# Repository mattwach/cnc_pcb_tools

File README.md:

# CNC PCB Tools

This document discusses an entire end-to-end process of milling PCBs with
a "cheap" 3018 CNC machine (although other machines could also apply).

Part of that process, verifying the design and calibrating the machine, are
helped along with simple Python scripts that I created and am giving away
for free.  This document explains how to to use these optional tools in
the appropriate places in the process.

Even if you do not use the tools, I think there this document contains
helpful information, both for beginners and more experienced individuals
looking to compare notes.

### Effort Estimate

This ended up being a long document.  Does that mean that the process takes
a long time?  I don't think it does.  Here are some time estimates:

| Step         | Beginner / Small Project | Experienced / Small Project | Experienced / Medium Project |
|--------------|--------------------------|-----------------------------|------------------------------|
| Design PCB   | 3 hours                  |  1 hour                     | 4 hours                      |
| Create GCode | 1 hour                   |  10 minutes                 | 15 minutes                   |
| CNC Setup    | 1 hour                   |  15 minutes                 | 15 minutes                   |
| CNC Cutting  | 15 minutes               |  15 minutes                 | 1 hour                       |
| Learning     | 1 hour                   |  -                          | -                            |
| **Total**    | **~6 hours**             |  **~2 hours**               | **~ 6 hours**                |

Of course there are many variables.  For example, if you use someone else's
PCB layout, you can cut that out of the time needed.

## Disclaimer

I have tested these tools and process and they work well for me.  That said, I
accept no responsibility for any damage caused to either person or equipment
that occurs from following advice in this document or running any of the
provided or mentioned software.

If you are a beginner to CNC, I have special "Tips" sidebars throughout the
document the CNC section that should be helpful.

## Gallery

Let start by looking at some example results.

First, a fast rise edge generator, as explained in
[this video](https://www.youtube.com/watch?v=9cP6w2odGUc).
This one was created for through-hole parts.

Here is a simple SMD board that uses a 555 and counter chip to make a simple
LED light show.  This one is still on the CNC machine:

Here a simple voltage cutoff circuit I made that combines an ATTiny85,
MOSFET and a fuse for good measure.

Here is an [e-paper based clock](https://github.com/mattwach/epaper_clock)
that I designed earlier this year.  I created
the first copy using a CNC machine, then made 4 more using boards from
a fab.  The first CNC copy was very useful in helping me discover
most of changes I wanted to make to the design (mostly layout) before
submitting the PCB. 

## Why CNC a PCB?

I've tried the following methods:

   * Breadboard
   * Prototype Boards
   * CNC (this doc)
   * Ordering a PCB from a fab, such as [oshpark.com](http://oshpark.com) or [www.pcbway.com](http://www.pcbway.com)

I feel that all of these methods have their place - it just depends on the
project.  Below I'll give my opinion on each one while trying not to go
overboard:

### Breadboard

Breadboards are great for trying something out in a short time.  Parts are
also not "consumed" and can be reused.  Using prebuilt modules as components
makes wiring simple and there are many cheap ones available.

However, any interconnects in your design will be performance limited in terms
of frequency, stray capacitance, unintended resistance and lower reliability.
It's not all bad since you get to exercise some troubleshooting skills and
things seems to work fine most of the time.

Also the method is not suitable for anything permanent.

### Prototype Boards

Like a breadboard but with better reliability and more permanence.  Making
one of these is a bit labor intensive though and there are few economies of
scale when making multiple copies.  Frequency is also usually limited
due to the lack of careful layout, stray capacitances and the lack of
a ground plane.

## CNC

Simple double sided boards are easy (often just a few patch wires are required
on the back side and these can be executed by drilling holes and hand routing
wires on the back).  Complex double sided is possible but requires alignment
techniques that are out-of-scope for this guide.

Performance is excellent.  Both SMD and through-hole components are supported.

Soldering is less convenient than a manufactured PCB due to lack of a solder
mask.  Lack of a silk screen (labeling) means that you may need a PCB printout
to guide component placement.

Requires some learning to be successful - that's the purpose of this document!

### Chemical Etch

I have not tried this one yet (and am meaning to soon) but have read and
watched videos on the process.  Overall, it seems similar to CNC - perhaps a
bit easier to dial in the process and get good results.  There are some clear
downsides however.  One is having to work with some nasty chemicals that
literally dissolve metal.  A second drawback is that drilling holes and cutting
out the board are not handled by the process so you'll have to come up with
something.

## Ordering a PCB

If you need a lot of copies, > 2 layers, or have a complex design, this is your
route.  You also get a solder mask for easier soldering and a silkscreen to
label component and provide other notes.

Turn around latency is around a week.  Cost is in the $20-$60 range assuming
that your board design is perfect.  If not, you'll consume additional weeks and
$$$ on iterations (or you can try to hack in workarounds).

## CNC Trip Points

I think a reason that many people avoid CNC is the upfront learning
curve.  Breaking a bit is easy and the risk of doing so increases
for any of the following reasons:

   1. You use the wrong parameters (feed rate, cut depth) either because you
      don't know or accidently type in the wrong number somewhere.
   2. Your GCode file (which the CNC takes as an input) neglected to command
      the motor to spin up.
   3. You don't zero the machine properly.
   4. You don't build a height map or improperly set one up
   5. Your copper clad is bowed due to improper clamping
   6. You are using unnecessarily aggressive design constraints, such as a
      0.2mm track width when 0.4mm could work for your project.

I'm going to talk about how to mitigate each of the problems about so your
success rate and quality can be quite high.

## Process Overview

Here is an overview of the steps I will cover.  But first, let's acknowledge
that everyone's situation, available tools, and skill sets are different.  The
process I describe below is what works for me, your ideal process will likely
end up being different, but it's good know what works for others.

Also, there could be better or more efficient ways of doing the things I
describe below.  If you think that is the case, let me know!

An overview of the steps:

  * **Design the PCB** (printed circuit board).  Here you create (or get) a
    schematic and layout a PCB.  The PCB you layout can be used for many
    purposes.  For example, you could take the same PCB design, checmical etch
    it, CNC it and send it to a fab.  That said, an "optimal" layout will take
    the final manufacturing process into consideration.
  * **Plot the PCB** design in a universal format know as "Gerber".  Gerber format
    is one that PCB manufacturers will accept as input when then make boards
    for you.  If you are into 3D printing, you can think of Gerber as "STL
    for circuits."
  * **Convert the "Gerber" file to "GCode"**.  GCode is a text file of instructions
    for a specific model of automated machine (CNC machines, 3D printers and 
    others).  The GCode file tells the machine where to cut, how fast to cut,
    how deep to cuts, etc.  None of this information is in the Gerber file -
    the conversion step adds it in.
  * **Setup the machine, execute the `.gcode`**.  
  * **Finishing work**.  Just a little bit of post work for CNC and you are ready for
    soldering.

## Designing your PCB

Some PCB's needs very fine traces and spacing to allow for placement of tiny
SMD components.  These are possible with CNC but not an ideal first project.
While learning, a more forgiving project will help you be
successful as you learn.  Thus my suggested starter project is a simple SMD
button adapter for breadboards.

It's nice because:

   * Simple: No getting sidetracked on how the circuit works
   * Useful: A lot of buttons work so-so when fit in a breadboard.  This one
     give a very solid and reliable connection.
   * Small: It's fast and cheap to iterate and experiment with different
     settings.
   * Forgiving design: Thick traces (1mm) and large clearances (0.4mm) mean
     that the result can be usable even if the settings still need tweaking.

I'm going to use KiCAD.  I used to use Eagle but many agree that KiCAD has
surpassed it.  Eagle and many others will still work fine,
however, as they can all export Gerber plots.  Here is the schematic:

This design has two pin headers and 4 buttons.  For the Pin header PCB
footprint, I'm just using a pin header built into the standard library:

If you are just starting with KiCAD, one way to set the footprint is to click
on it in the schematic, then type "e" to bring up its dialog, where you can
select the footprint:

If this is new information for you, then I suggest watching some of
[John's Basement KiCAD tutorial](https://www.youtube.com/playlist?list=PL3by7evD3F51fKkyrUbH-PCdwPCWc9F8a)
(or similar).

Here are the SMD buttons I chose.  They are 6x3.5mm:

I could not find any footprints for these in the KiCAD library.  The
files probably exist somewhere on the internet, but it's really quite
fast and easy to make a custom one in KiCAD (using the Footprint Editor),
and that is what I did:

[John's Basement, video #12](https://www.youtube.com/watch?v=Rdm5lS_sYsc&list=PL3by7evD3F51fKkyrUbH-PCdwPCWc9F8a&index=14)
demonstrates how to do this.

Of course, you can just use the one I already placed in the `examples/`
folder if you are going with the same button and want to focus more on the
CNC steps.

Here is the completed/routed PCB.

> **Beginner Note** this circuit doesn't have a ground fill place
  because the schematic has no ground, which is a bit unusual.  For a design
  with a ground, you'll want to Google search how to do a "ground fill" in
  KiCAD as it can simplify wiring and help reduce electrical noise in your
  circuit.

One more thing about KiCAD PCB design.  If you choose `File -> Board Setup...`
in the PCB editor, you'll should see a dialog of settings, one of which is
`Design Rules: Constraints`:

Here, there is a "minimum clearance" and "minimum track width" setting that you
can use to make your CNC life easier (in trade for limiting the ability to
route tiny parts).  I think 0.4mm for both settings is a good setting because:

   * You can use bits with a thicker point of contact (e.g. 0.3mm vs 0.1mm).
     Thicker contact points will be harder to break.
   * If you cut a but deeper (or rougher) than expected, the conservative
     minimum track width setting will increase the chance there is still some
     metal there to complete the connection.

of course, this is *just for less-complex designs that can support it*.  Once
you have a dialed-in process, you can push these number as small as you want to
try for.

## Making Gerber & Drill Files

Regardless of what tool I used to design the PCB, I'll need to export the
design in a universal format that the next phase of the process can understand.
These files are known as "Gerber" files and are like a "PDF" or "STL"  for
circuits meaning that they capture only the shapes of the PCB layout and not
other information, such as the associated schematic.

In KiCAD, you create Gerber files using the `File -> Plot`.  Here is the dialog
with the settings I use:

Note that I'm only exporting the F.CU and Edge.Cuts layers.  If you were
sending these files to a Fab, they would want other layers, like the silkscreen
layer, but the CNC machine can not directly make use of these (at least not in
the process I describe here).

This particular design needs holes drilled for the pin headers and
that data needs to be exported too.  "Generate Drill Files..." in the dialog
above will bring up this one.

Output are "PTH" and "NPTH" files.  Those stand for "plated hole" and "non
plated hole".  This design only has plated holes but, if you have mounting
holes, then both files might have some data in them.

## Gerber to GCode (using Flatcam)

There are a number of tools to do this as well.  One that I like is
[Cambam](www.cambam.info), which is a great all-around CNC program that can
import the files above.

But Cambam is not a free program so we are going to go with Flatcam, which is
free.  Flatcam is a bit more complex than it needs to be and is not bug-free
but it get's the job done once you find a navigation path through it's large
set of options.

Let's start the software:

> **Tip** The very first thing I recommend doing is saving your project.
  I also suggest adding the project file to version control.

Let's load up all of the Gerber files

and drill files

and here is the design loaded:

Note the horizontal and vertical red lines.  These will be the [0, 0] origin of
the CNC machine.  It's not in a good spot above because, I forgot to check "Use
drill/place origin" in the KiCAD Gerber plot dialog.  I can go back to KiCAD and
replot but flatcam has a tool as well:

You can put the origin wherever you want and may wonder why I didn't choose the
bottom left corner (as the bottom left aligns better with CNC coordinates).
The reason is because of where I solder my heighmap probe.  I cover the
details in the CNC section.

Now is a good time to save the project.

### Copper Isolation GCode

Now we are going to start making GCode, starting (arbitrarily) with the
copper layer.  Select the copper layer, then "properties":

The properties dialog is a launchpad for doing a number of things.  For the
copper layer, we want to choose "Isolation routing"

Now we are here:

#### Step 1

   * Here we choose the bit type and properties.  These settings are complexity
     overkill, in my opinion.  The intent is that the tool wants to help
     you calculate the needed depth for V bits to get the isolation width
     you want.  The reality is that the tool assumes your machine and process
     have perfect tolerances (e.g. no bit runout, perfect cuts, perfect
     positioning).  If any of these are untrue (and the probably are on a
     3018), then you just end up putting in adjusted numbers anyway to get the
     final result to come out.

   * To keep it simple, I directly choose the final cut width.  I do this
     by choosing a "C1" bit type and typing in the expected cut width.
     I'm essentially telling the tool "trust me, the cuts will be 0.39mm wide".
     If the real cuts are a little wider or narrower, it's usually not a problem
     unless the real cuts are so much wider that you lose copper traces.

   * I chose 0.39mm because I chose 0.4mm isolation widths in KiCAD.  See
     The KiCAD Design section above for a refresher on how I did this.
     **You need to choose a smaller number in flatcam than kicad** or flatcam
     will silently omit traces where it can't fit a line.

   * Keeping it simple makes the "Add from DB" section irrelevant so we can
     skip it.

#### Step 2

   * The main options here are "Passes" and "overlap"

   * Passes are the number of cut lines to make around each trace.

   * Overlap is how much to overlap the passes.  Too little overlap will lead
     to small bit of copper remaining between each pass, which usually isn't a
     big deal, but doesn't look as nice.

   * "Follow" and "Isolation Type" can be kept at default settings.

#### Step 3

   * Create the geometry traces for out next step.  You can actually click
     this button multiple times (presumably with different settings) to
     create multiple geometries - then ignore, hide or delete the
     ones you are not planning to use.

#### Here are results with 3 passes and 25% overlap

#### and 2 passes and 10% overlap

Note that both are included in the project at this point.  I
like the three pass version better so I'm going to right click
on the 2 pass version and delete it.

> **Tip** Now is a good time to save (and possible version control snapshot)

One more step.  At this point we need to create the final gcode file.  To do
this flatcam needs more information.  Click on the geometry object, then properties:

and we are onto this dialog:

#### Step 1

   * This section helps you calculate your cut depth if you are using a V
     bit.  As I said earlier, I find it easier to choose the "C1" bit type
     and put in the depth myself.  Thus if you are following my path,
     **you can simply ignore this section**.

#### Step 2

   * Cut Z: How deep to cut.  A very important parameter.  With a V bit, it also
     will determine your cut width (deeper cuts wider due to the V shape).  Cut 
     depth also has a big effect on how likely you are to break a bit.  **When
     in doubt, choose a small number here, like -0.03** - the penalty of cutting
     too shallow is that you need to cut again deeper which is very quick to do
     with the tools I talk about later (candle_heightmaap_adjust.py).
   * Multidepth.  This setting allows, you to split your cut into multiple passes.
     Using my `candle_heightmap_ajust.py` tool, I can do this "at the machine" as
     needed, thus **I don't use this option for copper isolation**.
   * Travel Z: How high to hover the bit over the board when not cutting.
     **Defaults are fine** but your job will finish quicker on a complex board if
     you set it lower.
   * Feedrate X-Y: How fast to cut in the XY direction.  I use settings in the
     120 to 200 range and found through controlled experiments that the quality
     was similar.  There is surely too high of a setting where quality and bit
     health will suffer and of course that limit will depend on which bit you
     choose.
   * Feedrate Z: How fast to plunge.  I find the **default setting of 60 to be ok**
     and have not experimented further.
   * Spindle Speed: RPM of the motor.  With a stock 3018, this number is not
     accurate becuase these machines have no RPM sensor.
     **10000 basically means "full power"** which will be ~7500 RPM in with a
     typical 3018 stock motor.

#### Step 3

   * End Move X,Y,Z: Where you want the bit to end up when the job is done.
     **I find ending at a x,y of 0,0 is nice for changing to the next bit**.
   * Preprocessor: Used to tailor the GCode output to a type of machine.  If
     you have a 3018 machine, you probably want a GRBL variant.  You can also
     make your own template from an existing one - something to consider
     after you get more experience with the process.

#### Step 4

   * Click "Generate CNC object"

#### Now you have a "simulated" CNC plot and an option to save it.

Here is a quick look at what was saved:

    (G-CODE GENERATED BY FLATCAM v8.994 - www.flatcam.org - Version Date: 2020/11/7)
    
    (Name: breadboard_buttons-F_Cu.gbr_iso_combined_cnc)
    (Type: G-code from Geometry)
    (Units: MM)
    
    (Created on Saturday, 27 August 2022 at 10:30)
    
    (This preprocessor is used with a motion controller loaded with GRBL firmware.)
    (It is configured to be compatible with almost any version of GRBL firmware.)
    
    (... MORE COMMENTS REMOVED ...)

    G21
    G90
    G17
    G94

    G01 F120.00
    
    M5             
    G00 Z15.0000
    G00 X0.0000 Y0.0000                
    ( --- LOOK HERE --- )
    T1
    (MSG, Change to Tool Dia = 0.3900)
    M0
    G00 Z15.0000
            
    M03 S10000.0
    G01 F120.00
    G00 X2.0236 Y-7.7442
    G01 F60.00
    G01 Z-0.0500
    G01 F120.00
    G01 X2.0370 Y-7.7495 F120.00
    G01 X2.0923 Y-7.7691 F120.00
    G01 X2.1584 Y-7.7856 F120.00
    G01 X2.2259 Y-7.7957 F120.00
    (... MORE COMMANDS ...)

Check out the `LOOK HERE` section above.  My particular machine does not like
the `T1` (tool change) code.  I can just delete it and move on but this is an
extra step.  Creating a custom template (beyond the scope of this document but not
hard), can allow the generate file to never add the code.
The takeaway for now is that the CNC "dry run", explained later,
might produce errors and these errors might require you to change the gcode file a
bit.

Another thing to look for is the `M03 S10000.0` line.  If you forgot to set your
RPM (left it at zero), this line will be missing and you will be sad when the
not-spinning bit breaks on the copper plate.  Checking cut depth is also advised.

Wouldn't it be nice if the computer did all of this checking for you?
I the tools I have included do exactly that (`check_pcb_cu.py <filename>`)
Computers are way better than me at checking everything so I just run the
check tool every time to help find unintentional "typo" settings I put into
flatcam.  For example, I once put -0.5mm instead of -0.05mm for my cut depth
and broke 3 bits before disovering it! (which led to my creating the check
tool to begin with).  More details on that later...

Anyway, lets move on to the other cuts.

### Drills

I'll arbitrarily work on the drills next.
First I disable (not delete) the isolation geometry and CNC cuts to clean up
the plot a bit:

Taking a look at the dialog

Number 1 above is the "Excellon Editor".  For this project we have 8 holes
to drill and they are all the same size so **we don't need this option**.
But, this option *is* often useful as it is often the case where you have
several drill sizes (like 0.85, 0.9, 0.95) and you want to combine
them all into a single size (all 0.9 for example) to make your drilling
process easier.

Number 2 is the drilling tool.  Lets click it:

   1. The drills you want to include in this file.  We only
      have one type in this example, so nothing futher to do here.
   2. How deep and fast you want to drill.
     * Cut Z: should be the same as your board thickness, maybe plus 0.1mm or so.
     * Multidepth:  Should not be needed for drilling
     * Travel Z: hover height.  default is fine.
     * Feedrate Z: cut speed.  Depends on the bit you use and the
       diameter of the hole.  For small holes, the 300 setting is fine.
     * Spindle Speed: Explained in the previous (copper) section
     * Offset Z: It's just added to Cut Z for tapered bit.  Or you
       could have just changed Cut Z directly so I'm not sure why this
       exists.
   3. It's all the same as the copper section (common parameters)
   4. Click here to make your drills

Now the drill paths are made and it's time to save the gcode file:

Let's move onto the final cut, the edge cuts (cutting out the board outline).
Again, I disable unneeded plots to clean up the display a bit.

### Edge Properties

   1. Set this to the diameter of your cutout bit.  I usually do with
      something in the 2-3mm range here (and all have worked fine)
   2. The defaults as-shown work fine for me.  Set Cut-Z to the thickness of
      your board plus 0.1mm.  Here we do want "multidepth"
      selected so that the bit takes several passes to do the cut as trying to
      cut everything in one pass would put a lot of load on the cutting bit.
   3. I have "Bridge Gaps" set to none.  If you set it to something else
      (like 4), then the CNC machine will leave small tabs that connect the
      board to the copper clad.  This is important or not important depending
      on how you have your copper clad secured.  I use the "double sided tape"
      method (described in the CNC section) so I do not need any tabs.

 When you are all set, click on "Generate Geometry" (top one).  On my version of
flatcam, I had to manually select the "properties" tab after doing this but
you might not need to.

   1. Verify this is the width of your cutting bit
   2. The parameters are similar to the copper section except that
      we are going with multidepth for this cut.  Make sure spindle
      RPM is not zero.
   3. The common section is the same as the copper section.  Make
      sure that the Preprocessor is set as-described in the copper section.
      Note that changing the Preprocessor can mess with other settings so
      check them over after making any changes.
   4. Generate the tool paths

All that is left to do is export the gcode:

And we are done!  It may have seemed like a lot of work but it goes pretty
quick (a few minutes) after you've done it a few times.  The bigger issue is
accidentally putting in a wrong number somewhere.  I have a solution that I
describe in the next section.

I suggest saving your project and check it into version control.  I also like
to commit all of my gcode files to version control so I can look at them later
if need-be.

### CGode Validation (Optional)

Sometimes when driving the creation tools (in this case KiCAD and Flatcam), I
accidentally enter an incorrect value in one of the parameter dialogs.  The
example I'll share is that I once entered -0.45mm for a z-cut depth into the
copper - what I meant to enter was -0.045mm.  The result what that I broke a
$15 bit and two more $2 bits before finding the problem.

The solution I came up with is "validation" scripts.  These are simple [Python](python.org)
scripts that you feed your final GCode into.  They read in the code and look
for problems.  The problem I mentioned in the previous paragraph will be caught
by the checking program along with many others.  Which problems exactly?  Well that is
ultimately up to you.  I provide my own configuration and I tried to make it
easy to modify it for whatever things you want to check - you can make it as
rigid or flexible as you want.

Here is the actual output of running the three gcode files I generated earlier in
Flatcam.

First the copper check.

    python3 check_pcb_cu.py breadboard_buttons-F_Cu.gbr_iso_combined_cnc.nc
    
    Properties:
      lines: 5063
      codes: 5029
      units: {'MM'}
      xrange: 0.0 .. 19.814
      yrange: -19.664 .. 0.0
      zrange: -0.05 .. 15.0
      max_plunge_feed_z: 60.0
      max_cut_feed_xy: 120.0
    
    Spinning in material: OK
    min_x: 0.0 > -1.0: OK
    max_x: 19.814 < 60.0: OK
    min_y: -19.664 > -40.0: OK
    max_y: 0.0 < 1.0: OK
    min_z: -0.05 > -0.1: OK
    max_z: 15.0 < 15.1: OK
    max_z_plunge: 0.05 <= 0.05: OK
    max_plunge_feed_z: 60.0 <= 61.0: OK
    max_cut_feed_xy: 120.0 <= 180.0: OK
    T1 not present: OK

Let's dig into this one a bit.  The first thing the script does is read the
file. Then some basic properties are printed.  These are just informational.
Finally the checks. Now let's look at the `check_pcb_cu.py` script that we ran:

    #!/usr/bin/env python3
    
    import check_gcode
    
    check = check_gcode.GCodeChecker()
    check.dump_properties()
    check.assert_spinning()
    check.assert_gt('min_x', check.min_x(), -1.0)
    check.assert_lt('max_x', check.max_x(), 60.0)
    check.assert_gt('min_y', check.min_y(), -40.0)
    check.assert_lt('max_y', check.max_y(), 1.0)
    check.assert_gt('min_z', check.min_z(), -0.1)
    check.assert_lt('max_z', check.max_z(), 15.1)
    check.assert_lte('max_z_plunge', check.max_z_plunge(), 0.05)
    check.assert_lte('max_plunge_feed_z', check.max_plunge_feed_z(), 61.0)
    check.assert_lte('max_cut_feed_xy', check.max_cut_feed_xy(), 180.0)
    # T1 may not be supported by your CNC machine
    check.assert_false('T1 not present', check.has_code('T01'))

This script is a simple set of rules.  Note how the checks in `check_pcb_cu.py`
match right up with the output printed when the tool is run.

You can definitely change rules, add your own or remove rules to mold the
checks to work with your setup.  Here is a basic list of *aggregation*
functions that you can choose from (all coded up in the
relatively-straightforward `check_gcode.py` file):

> Note: An aggregation takes a set of values and returns a single one.

   * `min_x(), min_y(), min_z()`: These represent the minimum bit coordinates
     present in the entire gcode file.  Checking these allows us to tell if we
     put the origin in an unexpected spot, accidently chose too big of a design
     to cut, or accidently set a final cut depth too deep.
   * `max_x(), max_y(), max_z()`: These represent the maximum bit coordinates
     present in the entire gcode file.  Checking these allows us to assert
     the design is not too big and that the final z position is not too high,
     where it would be in danger of striking hitting it's upper limit.
   * `max_z_plunge()`: This represents the maximum single-step change in z
     while cutting.  Changing Z too much in a single pass can break a bit.
   * `max_plunge_feed_z()`: This represents how fast the bit plunges into
     the PCB.
   * `max_cut_feed_xy()`: This represents the maximum cut speed in XY
     plane (across the surface of the PCB).
   * `has_code()`: This returns True if a gcode (such as `T01`) is found anywhere
     in the file.  This is useful for detecting codes that your machine does
     not know how to process.

Below are some asserts that you can wrap around the aggregations above.
An assert is like an "if" statement, where failing the assert will lead to the
program returning an error when it exits:

   * `assert_true(message, condition)`: Fails with `message` if `condition` is
     false.
   * `assert_false(message, condition)`: Fails with `message` if `condition` is
     true.
   * `assert_gt(message, value, reference)`: Fails with `message` if `value` is <= `reference`.
   * `assert_lt(message, value, reference)`: Fails with `message` if `value` is >= `reference`.
   * `assert_gte(message, value, reference)`: Fails with `message` if `value` is < `reference`.
   * `assert_lte(message, value, reference)`: Fails with `message` if `value` is > `reference`.
   * `assert_spinning()`: Fails if the bit is ever not spinning when `z < 0.0`

See the existing files for real-world examples.  Feel free to add your own
checks or functions as needed.

Back to the example, here is example output from the drill checker:

    python3 check_pcb_drill.py breadboard_buttons-PTH.drl_cnc.nc 
    Properties:
      lines: 95
      codes: 47
      units: {'MM'}
      xrange: 0.0 .. 14.224
      yrange: -18.034 .. 0.0
      zrange: -1.7 .. 15.0
      max_plunge_feed_z: 300.0
      max_cut_feed_xy: 0.0
    
    Spinning in material: OK
    min_x: 0.0 > -2.0: OK
    max_x: 14.224 < 60.0: OK
    min_y: -18.034 > -40.0: OK
    max_y: 0.0 < 2.0: OK
    min_z: -1.7 > -1.8: OK
    max_z: 15.0 < 15.1: OK
    max_z_plunge: 1.7 < 1.8: OK
    max_cut_feed_xy: 0.0 <= 0.0: OK
    T1 not present: OK

and finally the edge checker:

    python3 check_pcb_edge.py breadboard_buttons-Edge_Cuts.gbr_cutout_cnc.nc
    Properties:
      lines: 280
      codes: 245
      units: {'MM'}
      xrange: -1.096 .. 21.924
      yrange: -21.924 .. 1.096
      zrange: -1.7 .. 15.0
      max_plunge_feed_z: 60.0
      max_cut_feed_xy: 120.0
    
    Spinning in material: OK
    min_x: -1.096 > -2.0: OK
    max_x: 21.924 < 60.0: OK
    min_y: -21.924 > -40.0: OK
    max_y: 1.096 < 2.0: OK
    min_z: -1.7 > -1.8: OK
    max_z: 15.0 < 15.1: OK
    max_z_plunge: 0.6 <= 0.61: OK
    max_cut_feed_xy: 120.0 <= 120.0: OK
    T1 not present: OK
    Wrote /home/mattwach/git/kicad/breadboard_buttons/export/test.nc

Look at that last line.  The edge checker wrote out a gcode file because the
bottom if `check_pcb_edge.py` has this line:

    # the -1.0 padding account for an assumed 2.0 (or more) thick edge cut
    check.create_test_gcode('test_template.txt', 'test.nc', -1.0)

What is this new gcode file?  It is a rectangle that outlines your design with
a 1mm border and a z depth of 0.0.  What is that good for?  It is very useful
for machine calibration and verification.  More on that in the CNC section.

### CNC Setup

#### Machine Properties

The machine I'm working with is a 3018 Sainsmart.  I've also done this process
on a friend's differently-branded 3018 machine with success.  Many machines can
be made to work here but clearly some process adaptation will be needed.

#### Bit Choices

I did extensive and isolated testing on many different types and sizes of bits
to determine which ones I would use.  Below are the "winners" of this process,
along with sample images from the tests.

> Note: The result images are "before sanding".  When doing the tests, I thought
  that knowing how clean the cut was would be useful but I now think that post-sanding
  results would have been more useful.

##### Isolation routing

The first option is the 20 degree bits that come with many CNC machines.  These
bits can produce some fine traces and nice detail.  They are also quite cheap.

On the downside, they are not the designed for cutting PCBs and the associated
cutting stress exposes inconsistencies in quality.  I found that success with
these bits is a combination of cutting very slowly, not cutting too deeply and
getting a little lucky.

Many go for the 30 degree bits as an alternative.  These bits are a little
more robust than the 20 degree bits.  The trade-off is that cutting deeper
results in a wider track so you will not be able to get as
narrow of a track width as 20 degree if it matters (and for many projects
it does not).

Also I still think these are not an ideal choice verses the next two I will
describe.

Next up are 20 degree bits with an actual cutting flutes.  I find these
to be much more robust than the previously-mentioned bits.  They are
forgiving to a wider range of cutting speeds and depths.

The downside is the minimum track width - around 0.4mm.  This may
be a non-problem or a deal-breaker depending on your project.  If you
are just starting I recommend a project that can accept this width.

I final one I'll mention is a bit that is designed for isolation routing.
I find this bit give the best overall results.  But it is $15 a bit.  These
are also a bit more fragile than the 20 degree fluted bits and you need to
watch your cut depth more closely (because they are 45 degree bits) both
in terms of cut width and avoiding a breakage.

I feel this bit is one to "graduate to" after you are confident in your
process.

##### Hole drilling

For hole drilling, you can use special purpose drill bits:

or repurpose an end-mill bit for drilling

A specialized drill bit makes cleaner cuts but I find the end-mill to be
"good enough" for those cases where you don't have a correctly-sized
drill bit handy.

##### Board cutout

Here I find a standard end-mill bit in the 2-3mm range works well.

#### Dry Run

I highly recommend doing a dry run before doing your first real cuts.  After
you get a couple sucessful project behind you, you can skip the dry run.

To do this, first connect the Candle software to your machine and start it.
Next follow these steps.

   1. Remove any bit that is in the machine
   2. Use the jogging controls to place the motor head in a safe region.  If
      you are cuttiong someting small (as recommended), the middle of the machine
      and maybe 2cm (or so) away from the board is a good spot.
   3. Click Zero XY
   4. Click Zero Z
   5. Load one of your gcode files into candle (like the edge cut file, for example)
   6. Click the "check mode" option.
   7. Click "send". This sends each gcode to the machine in a special
      mode where the machine will give errors if it gets a code it doesn't like but
      will do nothing if everything is accepted.
   8. If all is good, unclick "check mode" and click "send" again.  Now the machine will
      start spinning up and moving - it thinks it's cutting but there is no bit loaded
      and plenty of clearance so you can just watch it for unexpected behavior.  Be ready to
      click "Abort" if anything looks like it is going wrong.
      
If the machine appears to be doing the right thing, repeat steps 5-8 for each remaning
gcode files (copper isolation, drills, test file)

You might see an unrecognized gcode error in step 7.  Often these are "tool
change" codes (M6, T1) that you can delete from the gcode file with a text
editor with no ill effects.  If in doubt, look up the gcode on Google.  For
future projects, you can change the "Preprocessor" in Flatcam (or make a custom
one) that permanently omits these codes.

#### PCB Preparation

##### Painters Tape Method

A lot of CNC projects shows the part being clamped down on the edges.  Besides
creating an obstacle that your CNC bit will need to avoid, this creates a
bowing issue where the pressure of the clamp can cause the middle of the PCB to
bow up.  The precision needed for a good quality cut is around 0.02mm so this
bowing is a problem.

The solution is to use the following process.

Take a piece of blue painters tape and put in on your machine.  I like
to use a small roller to make sure it's flat.

Put another piece of painters tape on the back of your PCB.  I use a roller
here too.

Add some CA to the painters tape on the PCB.  Try not to get the glue so close
to the edge that it makes a mess.

Optional: Add CA fixing spray to the tape on the machine (a mist of water also
works).  If you are willing to wait 20ish minutes for the CA to dry, this
step can be skipped.

Press the two pieces together firmly

##### Probe Preparation

If you are going to run a height map, which I recommend doing, you'll need to
get probes setup.  If you are unfamiliar, your CNC should have a couple of
terminals where you can attach wires.  On mine and many
controllers, this is at port A5 on the controller.  When these wires short together, the CNC
firmware receives a signal which it an interpret as "contact" between the bit
and the material.  Because the bit and copper PCB are metal, they can
participate in this electrical connection.

So you simply connect one probe to the bit and one to the board.
To connect to the board, I take a little piece of wire that I clipped of from a
resistor/capacitor/whatever of an old project and solder it to some upper
corner of the board (I go upper left).

When everything is connected, you should be able to test the "zero" feature of
your CNC software (I'm using candle)

> Tip: Doing a probe like this is a bit unnerving the first time as it will be the
  first end-to-end test of your setup.  If you have an appropriate mechanical
  spring lying around, you can use it as your "bit" for testing purposes with
  your hand at the abort button in case the probe fails and the spring starts to
  compress.

#### Loading the design

I start by loading the "test.nc" file I generated by the checking software in
the verification step.

> Tip: If you did not produce this file, you can use the edge cuts file instead.

#### Zeroing the machine

If you followed my method of putting the zero point in the upper left corner,
you can zero the XY of the CNC machine just a bit under the soldered probe pad -
or whever you want so long as the design will fit.

#### Generating a height map

The z tolerance for a quality copper cut is tight.  I'd say around 0.02 mm if you are
going for 0.4mm wide traces and even tighter if you are going smaller.

To get this kind of precision, a height map will help immensely.  The way a
heightmap works is that it probes your board in a grid-like fashion, then
alters the commands that will be sent to the CNC machine to conform to the
collected data.  The result is that you will see much better depth consistency.

To generate a height map in Candle, you first click on the "Create" button under the
"height map" section on the right:

And the bottom of the window changes to a setup UI:

   1. Click the autosize button to resize the map
   2. Pick a row and column count.  More will result in a better height map in
      trade for more probing time.  I think that a grid size of ~1cm is
      acceptable so I simply take the mm dimension / 10 + 1 and round up.  In this
      case, the design is 21x21mm so I'll go with (21 / 10 + 1 = 3).   Thus a 3x3 grid to
      get an acceptably-detailed grid.  If you need more precision (due to an
      uneven PCB or finer cuts), use larger numbers (e.g. 6x6).
   3. There are also "interpolation settings".  I always set these to the same
      values as the grid ones.
   4. Now look everything over one final time and click "probe" when you are
      ready to commit.  and the machine will start to collect data.  When it
      is done, you will see something like this:

   1. Go to the File menu and chose "save".  I name my file `height.map`.
   2. Click the "Edit" button to get back out.

   1. To actually use a heightmap click "Open"
   2. Make sure that the "use heightmap" option is checked.  As you check and 
      uncheck the option you should see the design slightly change, indicating
      that your heightmap is being applied.

#### Adjusting the height map

I found that for my 3018 machine, the height map process is precise but
not accurate.  Putting it another way, I'll see errors in the height map results
of 0-0.15mm BUT this error is consistent across every point so simply shifting
all of the points leads to a good result.

Here are two approaches for dealing with this.

The way I recommend is to generate a modified version of the heightmap.  The tool,
`candle_heightmap_adjust.py` is included in this project.  Here is how I use it:

    $ python3 candle_heightmap_adjust.py --input height.map --offset 0.1
    Wrote height_offset0.1.map

This creates an new heightmap file with the requested offset applied.  Let's
compare the raw data from the two files:

As you can see, the number were all simply shifted the requested offset.

> Tip: An *alternate* approach is to manually rezero the machine slightly. 
  Get the machine to z=0 (maybe take xy off the PCB surface to be safe), then
  click the "0.1mm" or "0.01mm" resolution and click z arrows the appropriate
  number of times in the desired direction.  Then click "zero Z".

Now we can use the loaded test file to validate our depth.

   1. Load the `heightmap_offset0.1.map` file into candle and make sure "use heightmap" is checked.
   2. Click "Send"

The machine will cut a rectangle outline which should only take a minute.

You resulting cut may not have cut anything at all.  That's because you told it
to cut at a height of 0.1mm (due to the heightmap file) above the board.  If
that is the case, try repeating with a `heightmap_offset0.05.map` file and keep
repeating in 0.05mm steps until you finally see the bit make contact.

**Or** 0.1mm might be your perfect number, in which case you'll see the
lightest of contact with the board, scratching the copper but not making it
through.

**Or** 0.1mm might be cutting through to the copper.  In this case, you'll want
to make a 0.15mm file and probably go with it assuming the 0.1mm cuts were no
too deep.  The example image represents this case.

You might also find that the number you choose is inconsistent in places on the
board (sometimes cutting sometimes not).  This can happen if the board is of a
lower quality and it not actually flat enough for your chosen grid points to
capture.  If this is the case, you'll probably need to cut in multiple passes,
each 0.05mm deeper, until all of your traces are good.  This will keep your
bit from breaking (as a result of cutting too deeply).  If it's really off,
you can start over with more heightmap points, on a different part of the
copper clad.

#### Cutting the copper

At this point, you should have a nicely-calibrated heightmap file (be it the
    original, or one with an offset applied) and you are ready to cut for real.
Load your copper gcode and *reload the heightmap* (which Candle clears out on
a load).  Choose the heightmap file that gave you good results:

When your cut is finished, vacuum the cut material away and inspect the board.

It may be obvious that the bit did not cut deep enough everywhere (likely due
to a lower quality PCB).  If this is the case, you can simply rerun the
`candle_heightmap_adjust.py` file with a height 0.05mm lower, load it into
candle and rerun the cut (alternately, use the manual rezero trick described
above).  There is no need to fully rezero the machine and, in fact, doing
so will cause more harm than good.  In really bad cases, you might need to
recut incrementally more than once.

After you think the cuts are deep enough, you can sand the board.  I use 400
grit first, then 1500 grit.  It's not a long process, just a few seconds with
each.  I then use a paper towel with some isopropyl alcohol on it for a final
clean.

Now I get out my multimeter and start poking around on the board.  The main
thing to look for is unexpected shorts.  I find this usually goes pretty well,
but the boost in confidence is worth the time.

#### Drilling the holes

Drilling holes is easy compare to the copper.  You just load a bit and
rezero the Z axis for the new bit.  *Do not rezero X or Y* as this will mess up the drill
locations. I zero Z using the "paper" method where I get the bit within 2 mm
of the surface, then set the Z increment to 0.1mm.  I then move a piece of
paper between the bit and PCB while moving it down in 0.1mm increments.  When
the paper sticks, I click the Z-zero button in Candle.

> **Note** You might think to use the probes to zero the drill bit.  If you do
so, make sure there is a conductive path to the bit as the isolation routing
process may have isolated your board from the probe.  I once broke a drill bit
because I didn't think about that!

You *can* use the heightmap file here but it's not necessary as the
need-for-z-precision is lower.

Watching the machine drill the holes so efficiently and precisely is one of the
highlights of the process for me.

You may have multiple drill sizes (and thus multiple gcode files).  Just repeat
the process above for each size.

#### Board cutout

A *relatively* straight-forward task.  Load up your endmill bit and z-zero it using the
same paper technique as described in the drilling section.

For this part, I'd consider wearing a mask as it creates the most material.  My
machine does not kick the material into the air or anything, but it's still
there.

### Finishing Up

Now that everything is done, you just need to dislodge the board.  I get if off
the surface by wedging in a flathead screwdriver and work at it on a side until
it comes loose.  I usually leave the rest of the PCB on the machine so I
(might) have fewer steps to do on the next board I cut.

#### Optional: Tinning

Copper oxides over time and may not be the easiest thing to solder.  You can
buy "liquid tin" to address these "problems".  I use quotes because I don't see
signs of oxidation on 1 year+ old boards I created and because I don't find
soldering to plain copper to be too difficult.  I still like to tin my more
complex designs though.

The process is simple but you'll want rubber gloves the entire process at a
minimum for protection:

   1. Find a plastic container.  One that is barely big enough to hold your
      board is ideal.
   2. Put your board in the container and pour the liquid tin on it.  Use as
      little as you can.
   3. Wait 7-10 minutes.  Gentle agitation of the container is probably helpful.
   4. Take out your board and rinse it in warm water.

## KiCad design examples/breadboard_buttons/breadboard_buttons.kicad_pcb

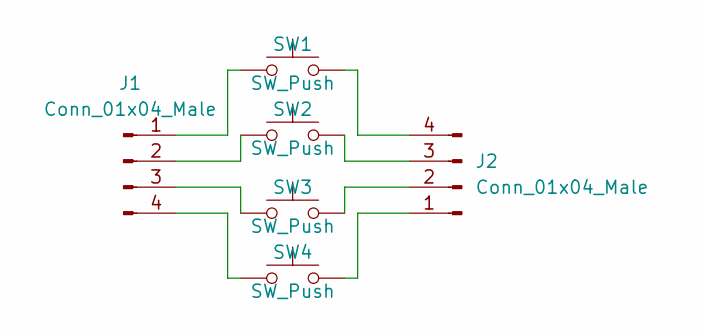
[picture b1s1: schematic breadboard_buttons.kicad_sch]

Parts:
J1, J2: Conn_01x04_Male; PinHeader_1x04_P2.54mm_Vertical
SW1, SW2, SW3, SW4: SW_Push; SMD_Button_6mm_3_5mm

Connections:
unnamed: J1.1, SW1.1
unnamed: J1.2, SW2.1
unnamed: J1.3, SW3.1
unnamed: J1.4, SW4.1
unnamed: J2.1, SW4.2
unnamed: J2.2, SW3.2
unnamed: J2.3, SW2.2
unnamed: J2.4, SW1.2

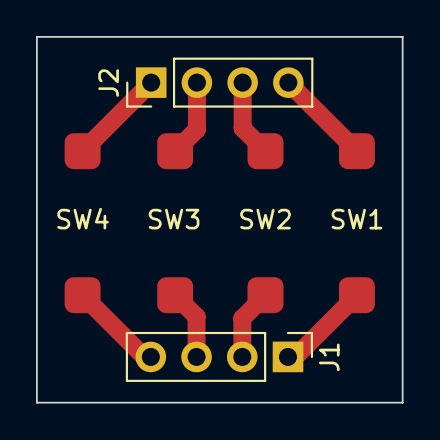
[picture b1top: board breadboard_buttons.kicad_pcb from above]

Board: 2 copper layers, 20.3 x 20.3 mm, 6 parts (0 on the bottom side), 8 nets.

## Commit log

2022-09-17 Initial copy from my private repro
2022-09-24 Slight grammer fixes
2022-10-01 Remove T1 check
2022-11-11 candle_heightmap_adjust.py: use grid settings not interpolation.
2023-05-01 Added stencil check
